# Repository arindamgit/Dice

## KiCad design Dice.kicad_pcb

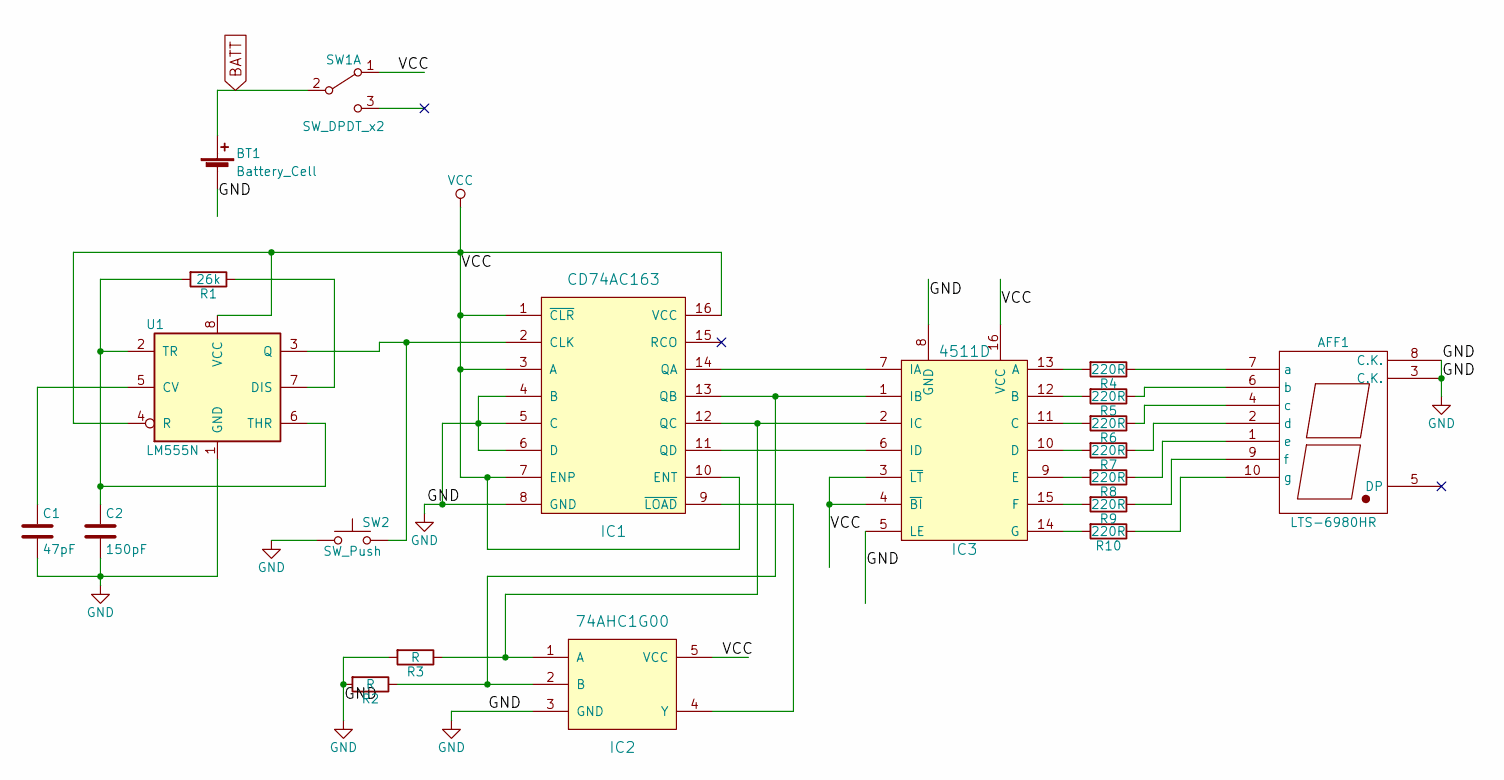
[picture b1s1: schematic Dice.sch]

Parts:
AFF1: LTS-6980HR; 7SegmentLED_LTS6760_LTS6780
BT1: Battery_Cell; BAT-HLDR-CR2032
C1: 47pF; C_0805_HandSoldering
C2: 150pF; C_0805_HandSoldering
IC1: CD74AC163; SO-16-N-HandSoldering
IC2: 74AHC1G00; TSOT-23-5_HandSoldering
IC3: 4511D; SO-16-N-HandSoldering
R1: 26k; R_0805_HandSoldering
R2, R3: R; R_0805_HandSoldering
R4, R5, R6, R7, R8, R9, R10: 220R; R_0805_HandSoldering
SW1: SW_DPDT_x2; SW_SPST
SW2: SW_Push; SW_PUSH_6mm
U1: LM555N; SOIC-8-N-Hand-Soldering

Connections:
BATT: BT1.1 (+), SW1.2 (B)
GND: AFF1.3 (C.K.), AFF1.8 (C.K.), BT1.2 (-), C1.2, C2.2, IC1.4 (B), IC1.5 (C), IC1.6 (D), IC1.8 (GND), IC2.3 (GND), IC3.5 (LE), IC3.8 (GND), R2.2, R3.2, SW2.1, U1.1 (GND)
unnamed: AFF1.1 (e), R8.1
unnamed: AFF1.2 (d), R7.1
unnamed: AFF1.4 (c), R6.1
unnamed: AFF1.6 (b), R5.1
unnamed: AFF1.7 (a), R4.1
unnamed: AFF1.9 (f), R9.1
unnamed: AFF1.10 (g), R10.1
unnamed: C1.1, U1.5 (CV)
unnamed: C2.1, R1.2, U1.2 (TR), U1.6 (THR)
unnamed: IC1.2 (CLK), SW2.2, U1.3 (Q)
unnamed: IC1.9 (~LOAD), IC2.4 (Y)
unnamed: IC1.11 (QD), IC3.6 (ID)
unnamed: IC1.12 (QC), IC2.1 (A), IC3.2 (IC), R3.1
unnamed: IC1.13 (QB), IC2.2 (B), IC3.1 (IB), R2.1
unnamed: IC1.14 (QA), IC3.7 (IA)
unnamed: IC3.9 (E), R8.2
unnamed: IC3.10 (D), R7.2
unnamed: IC3.11 (C), R6.2
unnamed: IC3.12 (B), R5.2
unnamed: IC3.13 (A), R4.2
unnamed: IC3.14 (G), R10.2
unnamed: IC3.15 (F), R9.2
unnamed: R1.1, U1.7 (DIS)
VCC: IC1.1 (~CLR), IC1.3 (A), IC1.7 (ENP), IC1.10 (ENT), IC1.16 (VCC), IC2.5 (VCC), IC3.3 (~LT), IC3.4 (~BI), IC3.16 (VCC), SW1.1 (A), U1.4 (R), U1.8 (VCC)

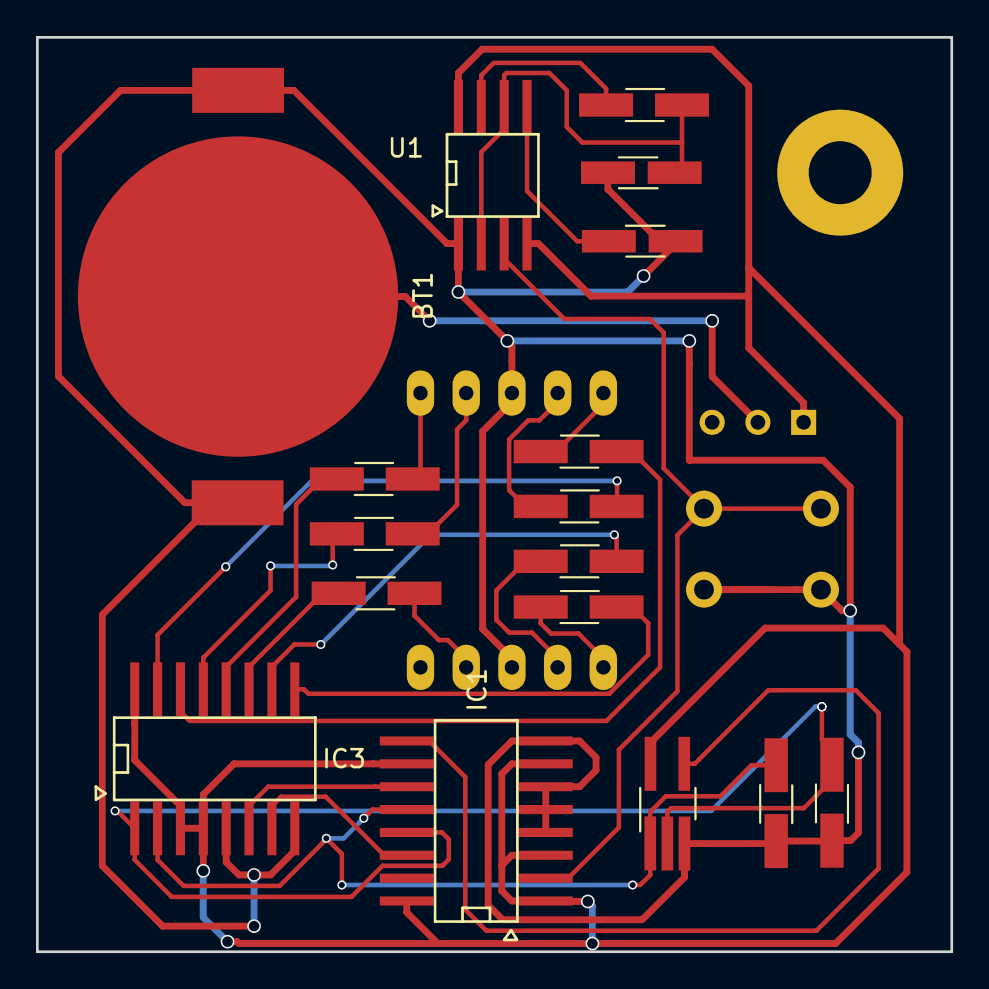
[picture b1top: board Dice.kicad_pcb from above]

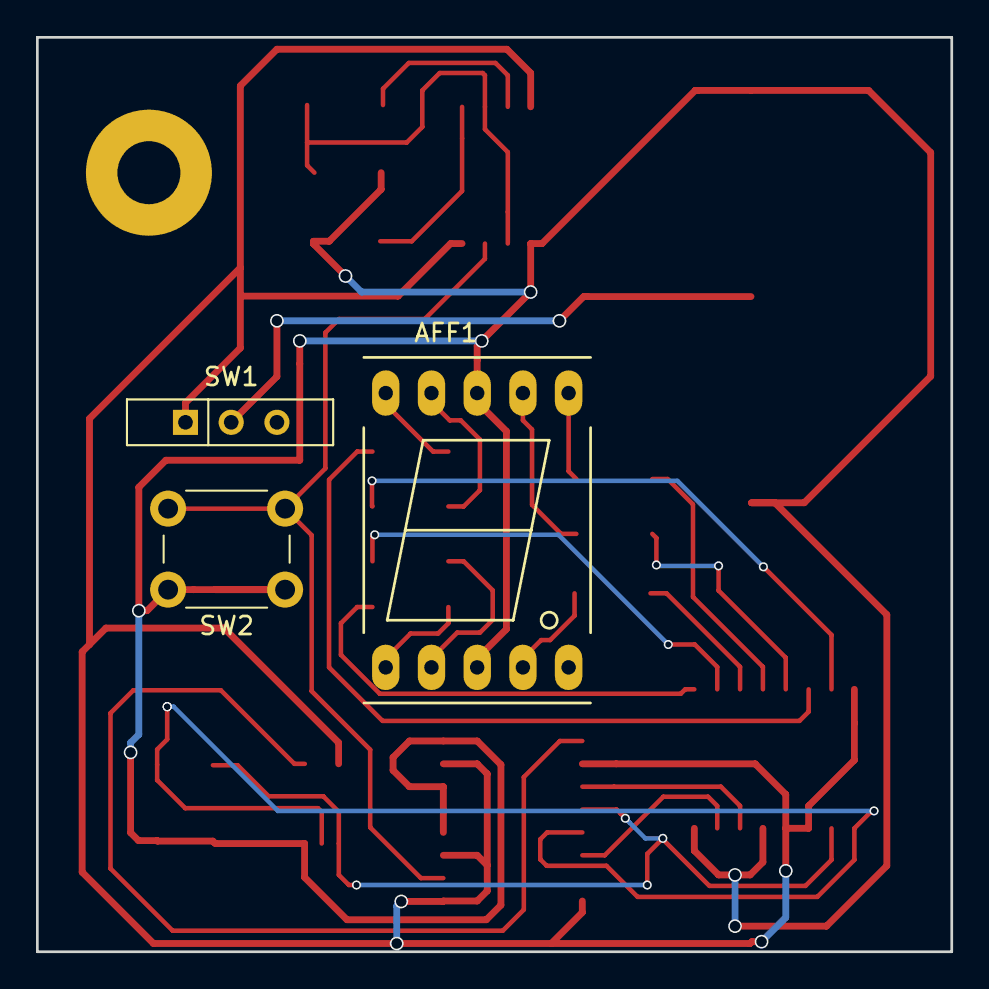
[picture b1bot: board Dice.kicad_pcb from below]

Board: 2 copper layers, 50.8 x 50.8 mm, 20 parts (3 on the bottom side), 26 nets.

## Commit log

2017-02-04 init
2017-02-04 added timer
2017-05-06 Dice revisited
